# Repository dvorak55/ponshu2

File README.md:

# ponshu2
The first keyboard in progress by Natural Keyboard Studio Murahana《叢華》.

## プロトタイプ写真  

自作キーボードを作っています、t-miyajimaです。  
現在、新プロジェクトを進めております。  
新プロジェクトの名前は『Ponshu2（仮）』です。  
これは、以下の特徴を持つキーボードを製造し、販売することが目的です。
- スタイリッシュで使いやすいキーボード
- レイヤードキーボードへの移行が簡単なキー配列
- 修理しやく、長年使い続けられるキーボード
- 配線は基板に頼らず、PCB部分をなるべく少なくする
- 製品全体の廃棄・製造時の環境負荷をなるべく低くする

# 環境負荷の低減
私は、2022年10月から2024年11月にかけて、自作キーボードを作るための工房を自作しました。  
その際に強く思ったのは、前世代の人間が残した遺物は、全て次世代の人間に受け継がれるのだ、ということです。  
そして、受け継がれた不要な遺物を片付けるのは、非常に大変だ、と実感しました。

次世代の人間のために不要な遺物をなるべく残さないようにする活動は、素晴らしいと思います。  
例えば、不要なものを分別してリサイクルすること。  
例えば、ゴミを捨てる際、処分に困るものが発生しないように工夫して物を製造すること。  
例えば、リサイクルしやすいように製造物に含有されるものを明示すること。  
私は、それらに取り組む人たちのことを非常に尊敬しています。

# 自然素材を用いた工房
私が自作したキーボード工房も、そのうち遺物になります。  
だから私は、工房を形作る素材に、自然素材を選びました。  
構造材には、鉄と木材（できる限り接着剤を含まない無垢材）を使用しました。  
断熱材には、炭、動物の毛（羊毛、羽毛）、綿や絹、紙を使用しました。  
これらは自然に還りやすく、片付けがしやすいです。  
また、再利用もしやすいので、次世代の人間がこうむる負担が減ります。  

# キーボードの目標
キーボードに用いる材料も、なるべく自然素材を多く使います。  
現在の私の能力では、コンピュータチップ周辺についてはPCBを使わざるを得ませんが、なるべくサイズを小さくします。  
キーボードのスイッチを保持するプレートには単純な金属を、キーボードのケースには木材を、配線には塩素等のハロゲンを含まないハロゲンフリー電線を、ハンダは鉛フリーハンダを、それぞれ用いる予定です。  
将来的に、より多くの部品を自然素材に置き換えることを目指しております。

# 進捗状況
2025年8月末の時点で、以下を進めております。
- 木材のケースへ取り付けやすく、配線しやすい基板の設計を開始
- キーボードプレートを木材のケースへ取り付けるための、真鍮ネジの選定
- 環境負荷の少ないハロゲンフリー電線の調達

また、以下は完了しております。
- キーボードのキーレイアウト
- キーボードプレートの試作
- キーキャップの試作
- Vialファームウェアの作成
- 試作機の動作テスト（この文章も試作機でタイプしております）

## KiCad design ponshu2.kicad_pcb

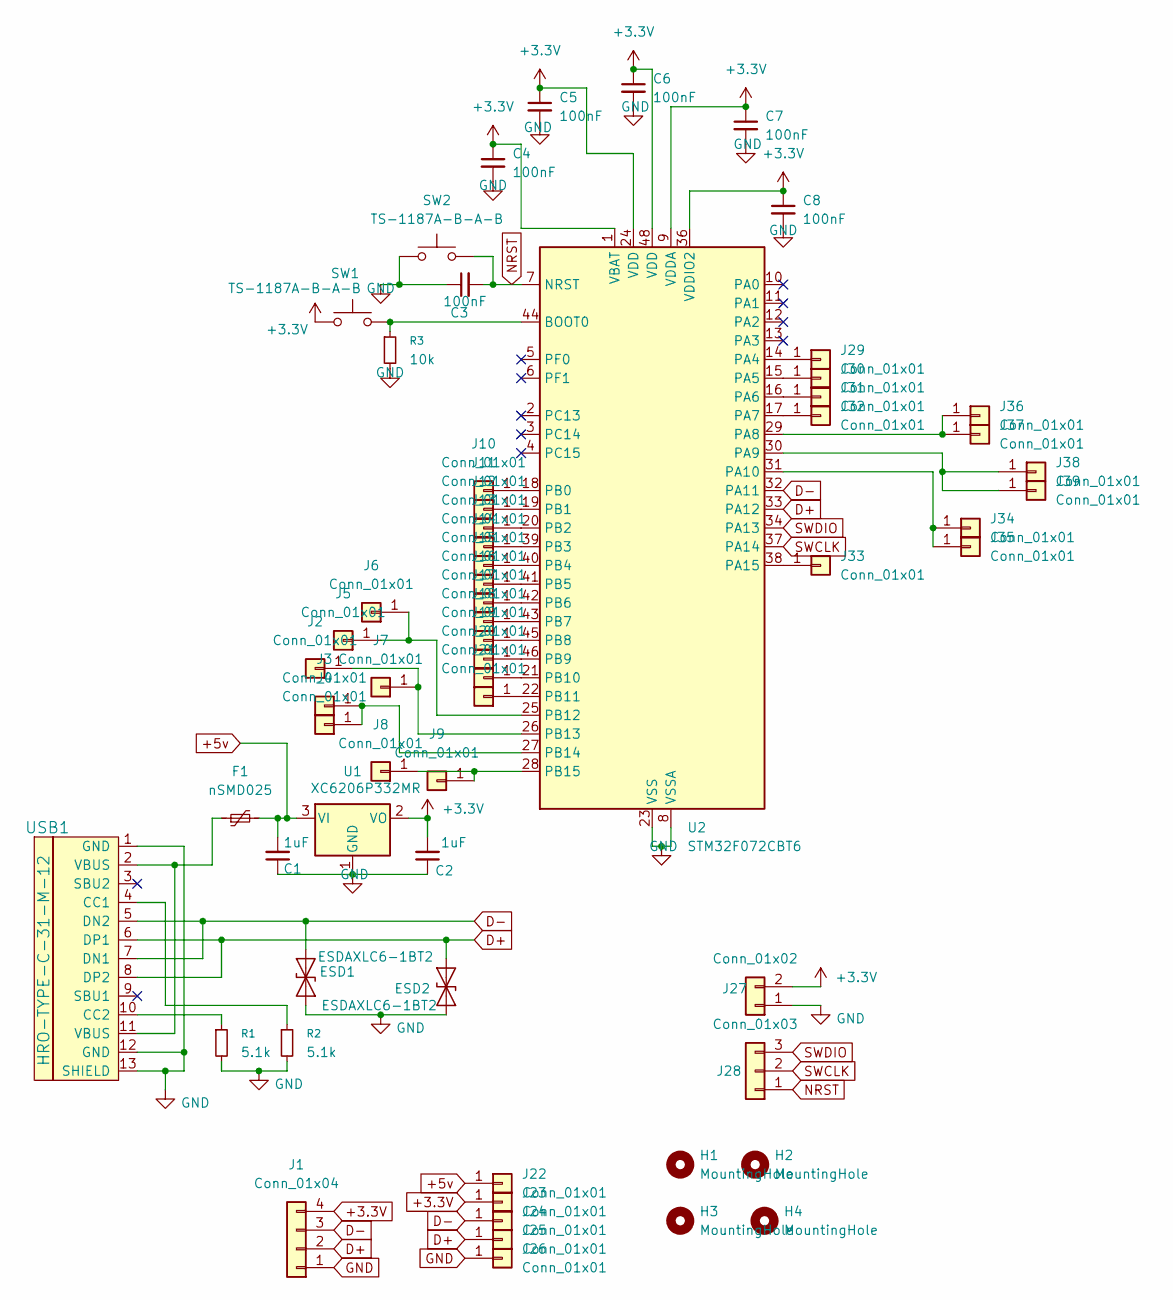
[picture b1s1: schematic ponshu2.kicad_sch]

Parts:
C1, C2: 1uF; C_0603_1608Metric
C3, C4, C5, C6, C7, C8: 100nF; C_0402_1005Metric
ESD1, ESD2: ESDAXLC6-1BT2; D_0402_1005Metric
F1: nSMD025; Fuse_1206_3216Metric
H1, H2, H3, H4: MountingHole; MountingHole_2.5mm
J1: Conn_01x04; PinHeader_1x04_P2.54mm_Vertical
J2, J3, J4, J5, J6, J7, J8, J9, J10, J11, J12, J13, J14, J15, J16, J17, J18, J19, J20, J21, J22, J23, J24, J25, J26, J29, J30, J31, J32, J33, J34, J35, J36, J37, J38, J39: Conn_01x01; PinHeader_1x01_P2.54mm_Vertical
J27: Conn_01x02; PinHeader_1x02_P2.54mm_Vertical
J28: Conn_01x03; PinHeader_1x03_P2.54mm_Vertical
R1, R2: 5.1k; R_0603_1608Metric
R3: 10k; R_0603_1608Metric
SW1, SW2: TS-1187A-B-A-B; SKQGADE010
U1: XC6206P332MR; SOT-23
U2: STM32F072CBT6; LQFP-48_7x7mm_P0.5mm
USB1: HRO-TYPE-C-31-M-12; HRO-TYPE-C-31-M-12-HandSoldering

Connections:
+3.3V: C2.2, C4.1, C5.1, C6.1, C7.1, C8.1, J1.4, J23.1, J27.2, SW1.1, U1.2 (VO), U2.1 (VBAT), U2.9 (VDDA), U2.24 (VDD), U2.36 (VDDIO2), U2.48 (VDD)
+5v: C1.2, F1.2, J22.1, U1.3 (VI)
D+: ESD2.2 (A2), J1.2, J25.1, U2.33 (PA12), USB1.6 (DP1), USB1.8 (DP2)
D-: ESD1.2 (A2), J1.3, J24.1, U2.32 (PA11), USB1.5 (DN2), USB1.7 (DN1)
GND: C1.1, C2.1, C3.1, C4.2, C5.2, C6.2, C7.2, C8.2, ESD1.1 (A1), ESD2.1 (A1), J1.1, J26.1, J27.1, R1.2, R2.2, R3.2, SW2.1, U1.1 (GND), U2.8 (VSSA), U2.23 (VSS), U2.35 (VSS), U2.47 (VSS), USB1.1 (GND), USB1.12 (GND), USB1.13 (SHIELD)
NRST: C3.2, J28.1, SW2.2, U2.7 (NRST)
unnamed: F1.1, USB1.2 (VBUS), USB1.11 (VBUS)
unnamed: J2.1, J7.1, U2.26 (PB13)
unnamed: J3.1, J4.1, U2.27 (PB14)
unnamed: J5.1, J6.1, U2.25 (PB12)
unnamed: J8.1, J9.1, U2.28 (PB15)
unnamed: J10.1, U2.18 (PB0)
unnamed: J11.1, U2.19 (PB1)
unnamed: J12.1, U2.20 (PB2)
unnamed: J13.1, U2.39 (PB3)
unnamed: J14.1, U2.40 (PB4)
unnamed: J15.1, U2.41 (PB5)
unnamed: J16.1, U2.42 (PB6)
unnamed: J17.1, U2.43 (PB7)
unnamed: J18.1, U2.45 (PB8)
unnamed: J19.1, U2.46 (PB9)
unnamed: J20.1, U2.21 (PB10)
unnamed: J21.1, U2.22 (PB11)
unnamed: J29.1, U2.14 (PA4)
unnamed: J30.1, U2.15 (PA5)
unnamed: J31.1, U2.16 (PA6)
unnamed: J32.1, U2.17 (PA7)
unnamed: J33.1, U2.38 (PA15)
unnamed: J34.1, J35.1, U2.31 (PA10)
unnamed: J36.1, J37.1, U2.29 (PA8)
unnamed: J38.1, J39.1, U2.30 (PA9)
unnamed: R3.1, SW1.2, U2.44 (BOOT0)
unnamed: R2.1, USB1.4 (CC1)
unnamed: R1.1, USB1.10 (CC2)
SWCLK: J28.2, U2.37 (PA14)
SWDIO: J28.3, U2.34 (PA13)

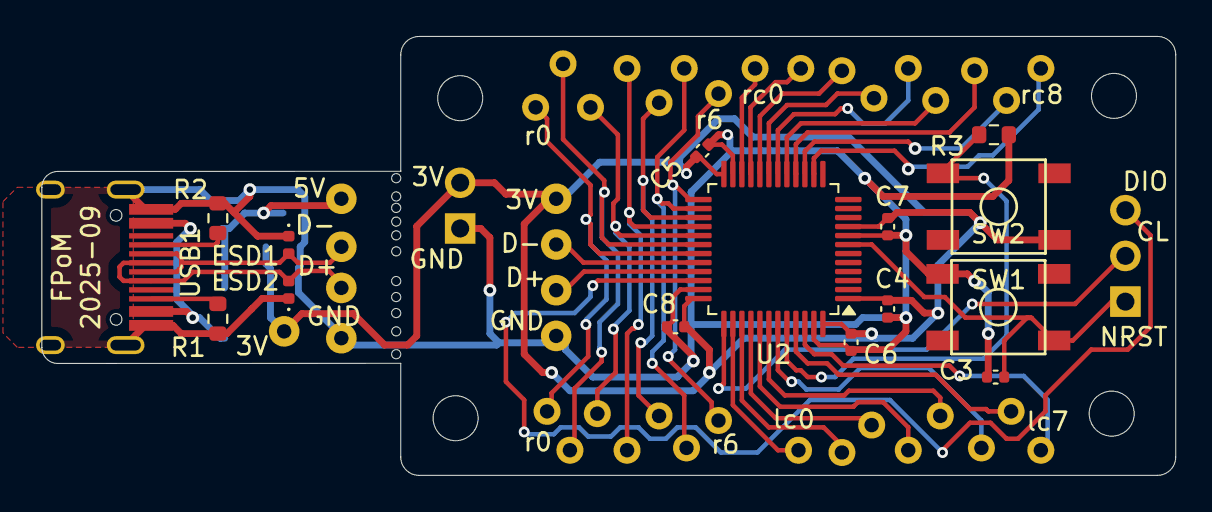
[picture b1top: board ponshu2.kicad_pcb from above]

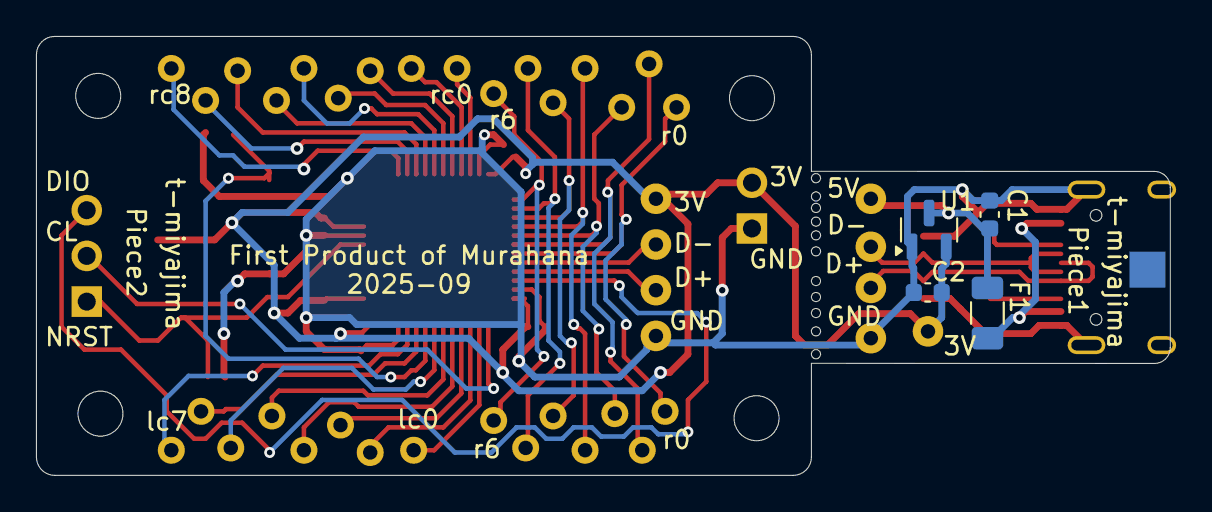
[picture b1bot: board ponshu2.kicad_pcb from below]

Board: 2 copper layers, 63.0 x 24.4 mm, 62 parts (4 on the bottom side), 36 nets.

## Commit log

2025-08-26 initialize project 2025-8-26
2025-08-26 readme photo upload
2025-08-26 Update README.md add photo of prototype
2025-08-26 auto update of kicad
2025-08-26 Add submodules
2025-08-26 add ai03(GOD) footprints
2025-08-26 create sch file
2025-08-30 chotto PCB tukutayo
2025-08-30 PCB daitai owatta kamo
2025-09-02 sukoshi susumeta
2025-09-02 kiban susumeta
2025-09-03 kiban susumetazo!
2025-09-03 kiban no ana kankaku hiroku shita
2025-09-04 kiban hobo kansei shita
2025-09-04 kiban kansei
    names of kiban are Piece1 and Piece2
